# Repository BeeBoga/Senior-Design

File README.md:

# Senior-Design
These are the files utilized in my senior design project which includes a PCB board design provided here, and integration with an arduino Mega 2560.
The main code that I believe is beneficial here would be the code used for the TLC5955 LED driver. There was not much information out there when I begain working on this at the time.
I was able to write functions to bit-bang the colors and intensity I wanted at "fast" speeds for an arduino since I used register manipulation directly

NOTE: the register manipulation will only translate perfectly to the same atmel chip used on said arduino board.

I have not gone back and cleaned this up, but I figured that I take from plenty of broken thoughts in the open-source world so I might as well give back what I have just sitting around incase it's useful to someone

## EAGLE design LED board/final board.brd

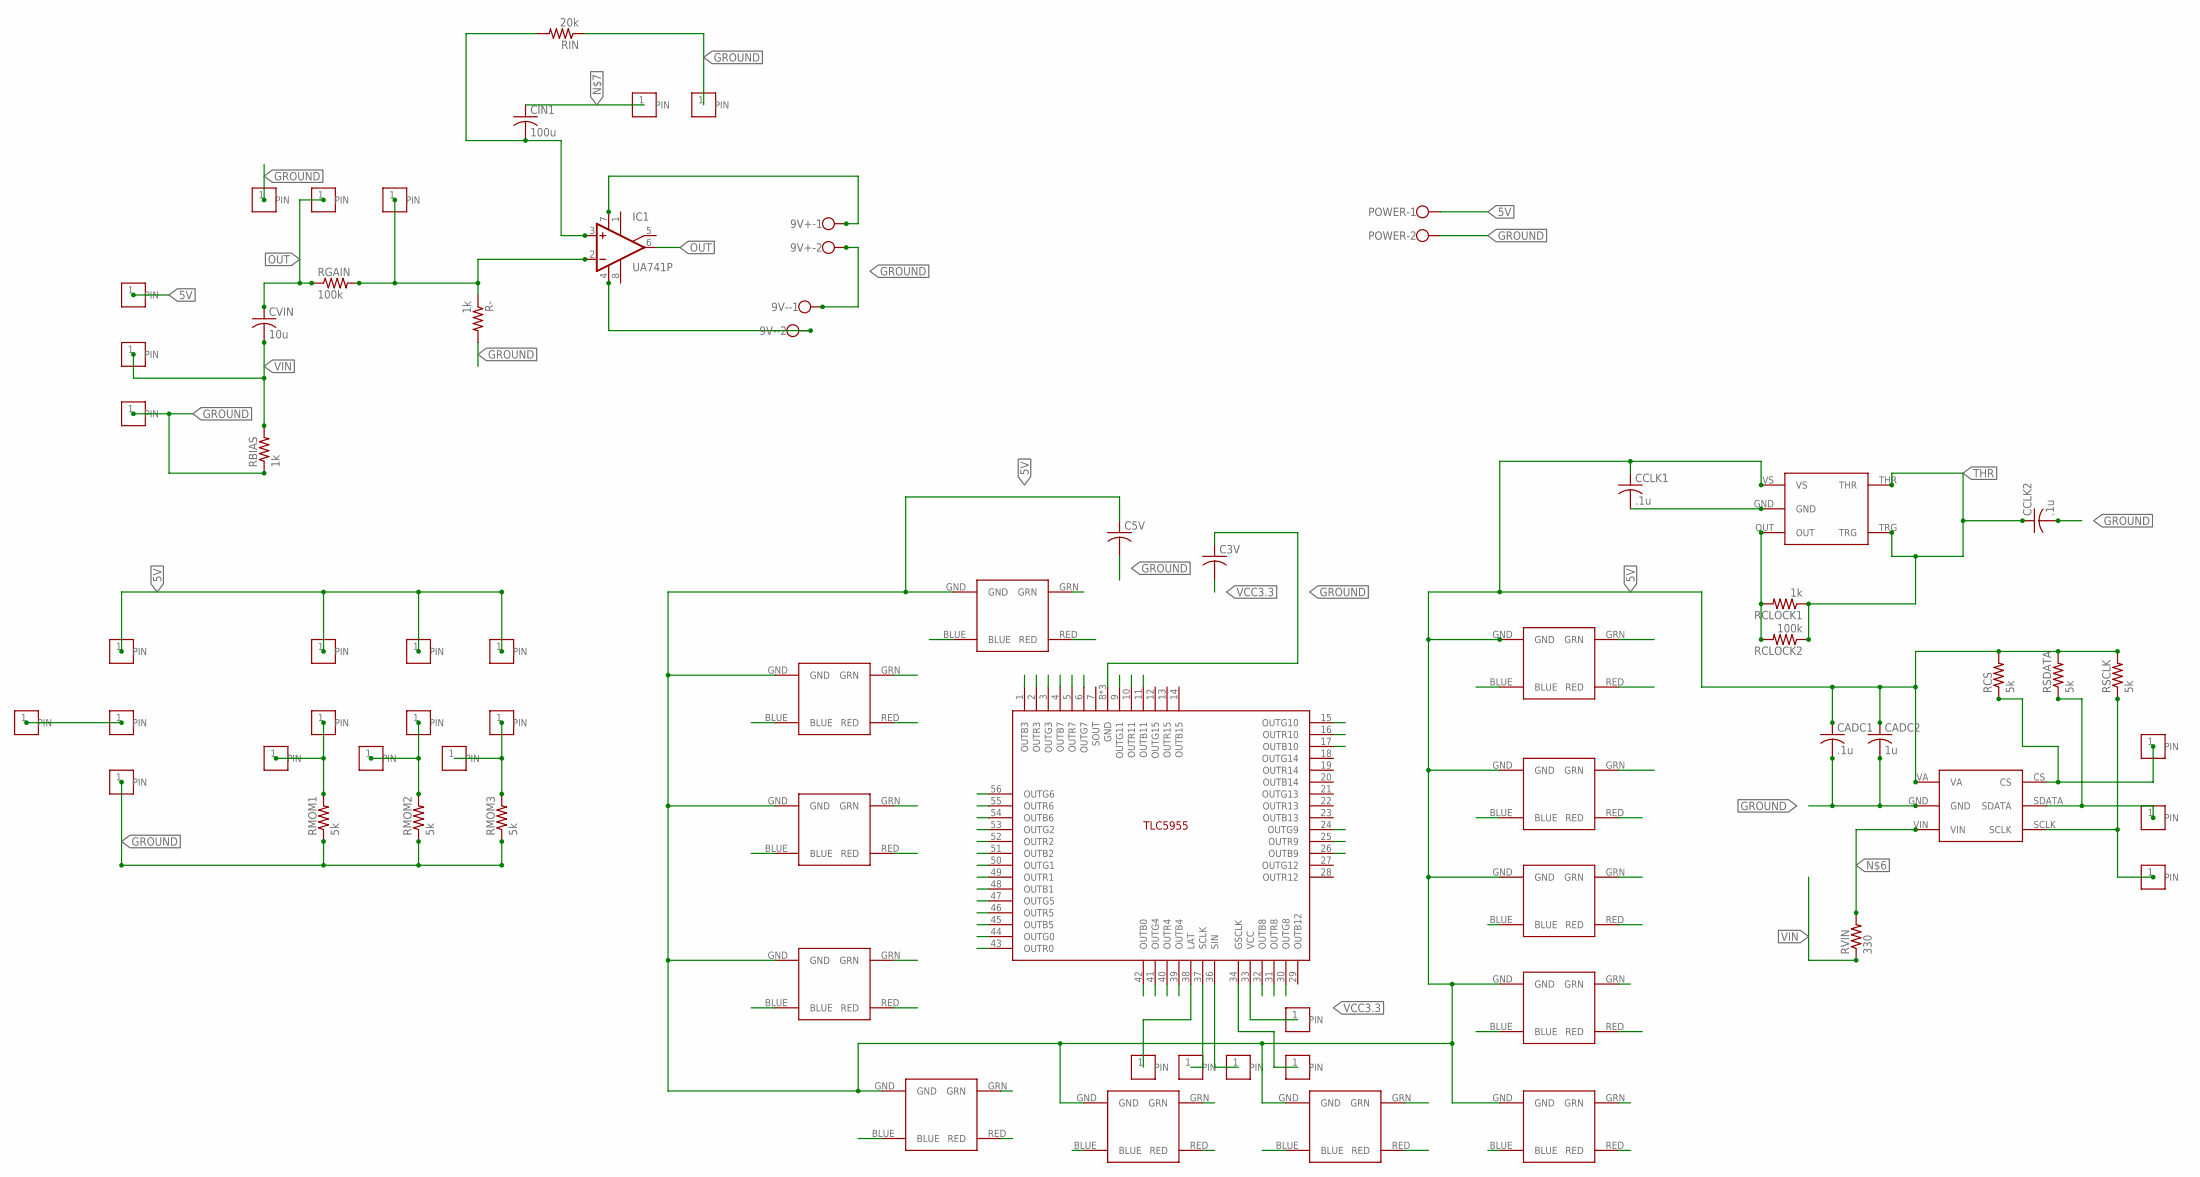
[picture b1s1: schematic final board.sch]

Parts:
3.3V: HEADERPIN_1
9V+, 9V-: W237-102
C3V, C5V: C-USC0805; C0805
CADC1: .1u; C0805
CADC2: 1u; C0805
CCLK1, CCLK2: .1u; C0805
CIN1: 100u; C0805
CS: HEADERPIN_1
CVIN: 10u; C0805
DATA: HEADERPIN_1
GSCLK: HEADERPIN_1
IC1: UA741P; DIL08
INPUTGND: HEADERPIN_1
INPUTV: HEADERPIN_1
INT1, INT2, INT3: HEADERPIN_1
LAT: HEADERPIN_1
MOMA1, MOMA2, MOMA3: HEADERPIN_1
MOMB1, MOMB2, MOMB3: HEADERPIN_1
POTAMPGND: HEADERPIN_1
POTAMPVAL: HEADERPIN_1
POTAMPVCC: HEADERPIN_1
POTBIAS5V: HEADERPIN_1
POTBIASGND: HEADERPIN_1
POTBIASVAL: HEADERPIN_1
POTLVL5V: HEADERPIN_1
POTLVLGND: HEADERPIN_1
POTLVLVAL, POTLVLVAL2: HEADERPIN_1
POWER: W237-102
R-: 1k; M0805
RBIAS: 1k; M0805
RCLOCK1: 1k; M0805
RCLOCK2: 100k; M0805
RCS: 5k; M0805
RGAIN: 100k; M0805
RIN: 20k; M0805
RMOM1, RMOM2, RMOM3: 5k; M0805
RSCLK: 5k; M0805
RSDATA: 5k; M0805
RVIN: 330; M0805
SCLK: HEADERPIN_1
SIN: HEADERPIN_1
SLK: HEADERPIN_1
TLC5955: TLC5954; TLC5955
U$1: MIC1555; SOT-23
U$2, U$3, U$4, U$5, U$6, U$7, U$8, U$9, U$10, U$11, U$12, U$13: KINGSBRIGHT_LED_3.5X2.8
U$14: ADC121S101; SOT-23(6)

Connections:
5V: C5V.1, CADC1.1, CADC2.1, CCLK1.1, MOMA1.1, MOMA2.1, MOMA3.1, POTBIAS5V.1, POTLVL5V.1, POWER.1, RCS.2, RSCLK.2, RSDATA.2, U$1.VS, U$2.GND, U$3.GND, U$4.GND, U$5.GND, U$6.GND, U$7.GND, U$8.GND, U$9.GND, U$10.GND, U$11.GND, U$12.GND, U$13.GND, U$14.VA
B0: TLC5955.42 (OUTB0), U$13.BLUE
B1: TLC5955.48 (OUTB1), U$12.BLUE
B2: TLC5955.51 (OUTB2), U$11.BLUE
B3: TLC5955.1 (OUTB3), U$10.BLUE
B4: TLC5955.39 (OUTB4), U$9.BLUE
B5: TLC5955.45 (OUTB5), U$8.BLUE
B6: TLC5955.54 (OUTB6), U$7.BLUE
B7: TLC5955.4 (OUTB7), U$6.BLUE
B8: TLC5955.32 (OUTB8), U$5.BLUE
B9: TLC5955.26 (OUTB9), U$4.BLUE
B10: TLC5955.17 (OUTB10), U$3.BLUE
B11: TLC5955.11 (OUTB11), U$2.BLUE
G0: TLC5955.44 (OUTG0), U$13.GRN
G1: TLC5955.50 (OUTG1), U$12.GRN
G2: TLC5955.53 (OUTG2), U$11.GRN
G3: TLC5955.3 (OUTG3), U$10.GRN
G4: TLC5955.41 (OUTG4), U$9.GRN
G5: TLC5955.47 (OUTG5), U$8.GRN
G6: TLC5955.56 (OUTG6), U$7.GRN
G7: TLC5955.6 (OUTG7), U$6.GRN
G8: TLC5955.30 (OUTG8), U$5.GRN
G9: TLC5955.24 (OUTG9), U$4.GRN
G10: TLC5955.15 (OUTG10), U$3.GRN
G11: TLC5955.9 (OUTG11), U$2.GRN
GROUND: 9V+.2, 9V-.1, C3V.1, C5V.2, CADC1.2, CADC2.2, CCLK1.2, CCLK2.2, INPUTGND.1, POTAMPGND.1, POTBIASGND.1, POTLVLGND.1, POWER.2, R-.2, RBIAS.1, RIN.1, RMOM1.1, RMOM2.1, RMOM3.1, TLC5955.8 (GND), TLC5955.35 (GND), TLC5955.HEATSINK (GND), U$1.GND, U$14.GND
GSCLK: GSCLK.1, RCLOCK1.2, RCLOCK2.2, TLC5955.34 (GSCLK), U$1.OUT
LAT: LAT.1, TLC5955.38 (LAT)
unnamed: CS.1, RCS.1, U$14.CS
unnamed: INT1.1, MOMB1.1, RMOM1.2
unnamed: RSCLK.1, SLK.1, U$14.SCLK
unnamed: 9V+.1, IC1.7 (V+)
unnamed: 9V-.2, IC1.4 (V-)
unnamed: RVIN.2, U$14.VIN
unnamed: CIN1.1, INPUTV.1
unnamed: CIN1.2, IC1.3 (+IN), RIN.2
unnamed: IC1.2 (-IN), POTAMPVCC.1, R-.1, RGAIN.2
unnamed: INT2.1, MOMB2.1, RMOM2.2
unnamed: INT3.1, MOMB3.1, RMOM3.2
unnamed: POTLVLVAL.1, POTLVLVAL2.1
OUT: CVIN.1, IC1.6 (OUT), POTAMPVAL.1, RGAIN.1
R0: TLC5955.43 (OUTR0), U$13.RED
R1: TLC5955.49 (OUTR1), U$12.RED
R2: TLC5955.52 (OUTR2), U$11.RED
R3: TLC5955.2 (OUTR3), U$10.RED
R4: TLC5955.40 (OUTR4), U$9.RED
R5: TLC5955.46 (OUTR5), U$8.RED
R6: TLC5955.55 (OUTR6), U$7.RED
R7: TLC5955.5 (OUTR7), U$6.RED
R8: TLC5955.31 (OUTR8), U$5.RED
R9: TLC5955.25 (OUTR9), U$4.RED
R10: TLC5955.16 (OUTR10), U$3.RED
R11: TLC5955.10 (OUTR11), U$2.RED
SCLK: SCLK.1, TLC5955.37 (SCLK)
SDATA: DATA.1, RSDATA.1, U$14.SDATA
SIN: SIN.1, TLC5955.36 (SIN)
THR: CCLK2.1, RCLOCK1.1, RCLOCK2.1, U$1.THR, U$1.TRG
VCC3.3: 3.3V.1, C3V.2, TLC5955.33 (VCC)
VIN: CVIN.2, POTBIASVAL.1, RBIAS.2, RVIN.1

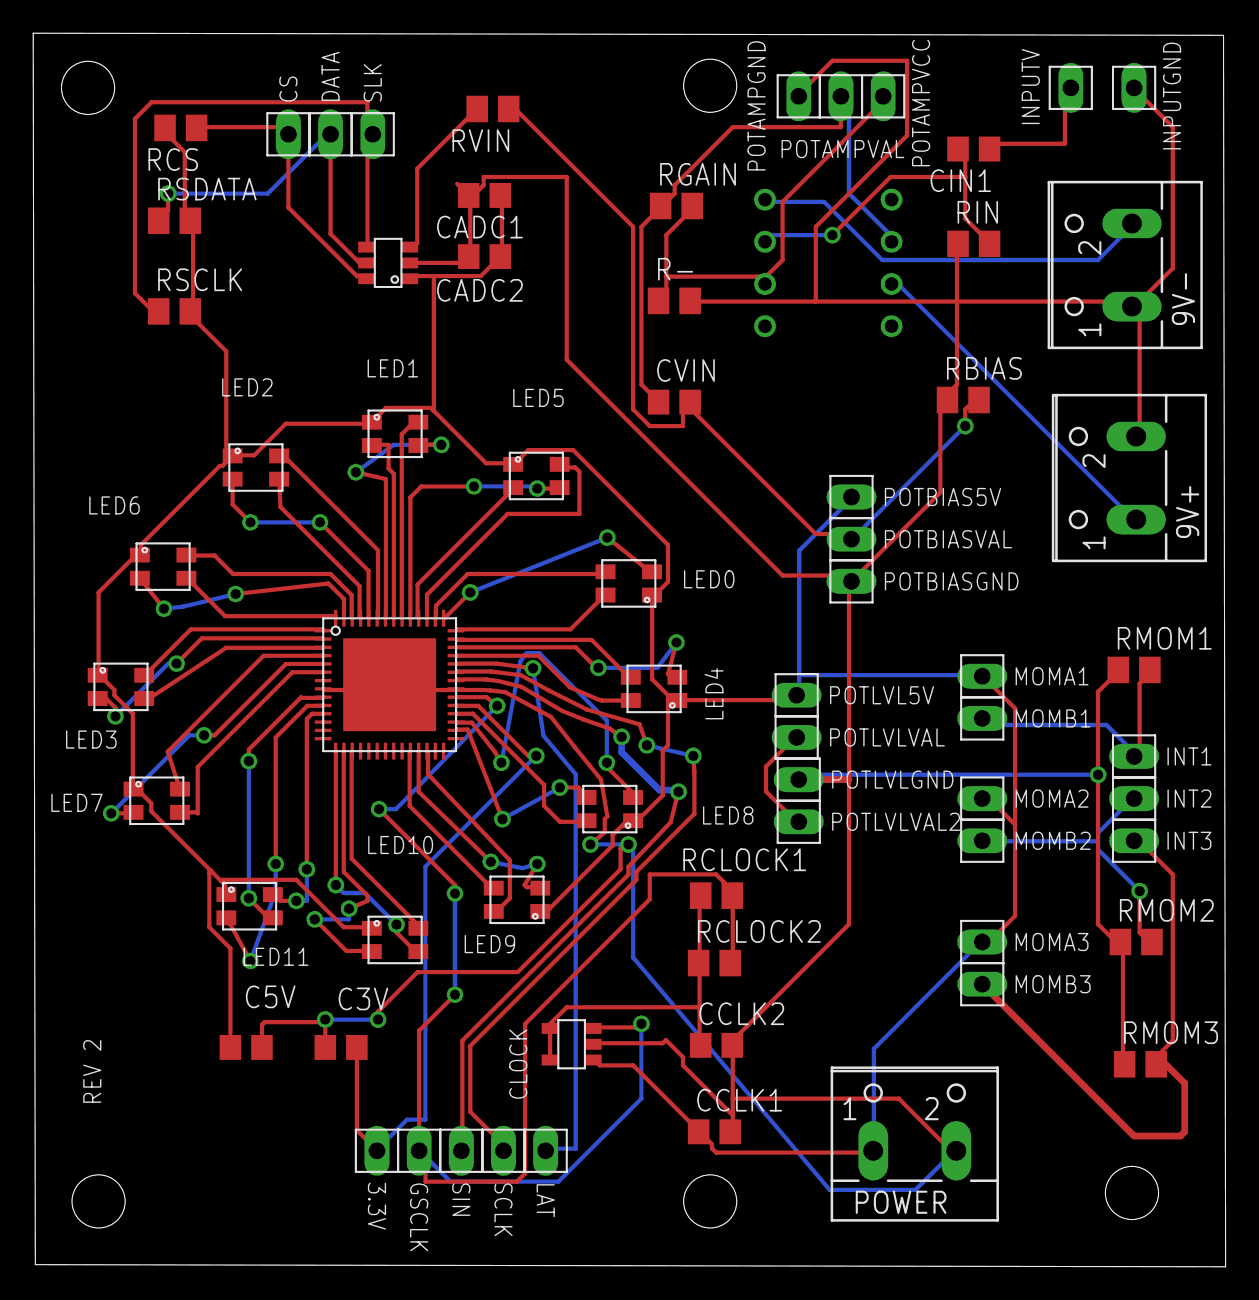
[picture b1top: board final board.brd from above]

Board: 2 copper layers, 71.8 x 74.3 mm, 69 parts (1 on the bottom side), 59 nets.

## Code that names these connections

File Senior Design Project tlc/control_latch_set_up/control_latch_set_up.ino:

#define LAT 7
#define SCLK 6
#define SIN 5
#define GSCLK 4

//769 bit register
//768th bit is control bit 0 sets grayscale
//1 sets dc,mc,bc,fc
//control latch is 371 bits long
//DC data latch is 336 bits long

//bits shift in from 0 towards 769
//in GS each color is 16 bits wide with bit 0 being OUTR0 bit 0 and bit 15 being OUTR0 bit 15

//msb == 1 stores here
//8 bit decoder 767:760
//bits 370:366 FC function control
//bits 365:345 BC global Bright starts at Rn,Gn,then Bn
//bits 344:336 MC max current starts at Rn, Gn, then Bn
//bits 335:0 DC dot correction 7 bits wide each first six are OUTR0



void setup() {
  // put your setup code here, to run once:

  int i, temp;
  int GS [49];
  int settings[769];
  int count =0;
  int times=0;
  int timetemp;
  int FC[5] = {0,0,1,1,1};

  pinMode(2, OUTPUT);

  //analogWrite(2, 128);

  Serial.begin(9600);

  /*
  GS[48]=0;

  for(i=0; i <49;i++)
  {
    if((i%3)==0)
      GS[i]=10000;
    else
      GS[i]=10000;
  }
  */
  
  pinMode(LAT, OUTPUT);
  pinMode(SCLK, OUTPUT);
  pinMode(SIN, OUTPUT);
  pinMode(GSCLK, OUTPUT);
  
  digitalWrite(SCLK, LOW);

  digitalWrite(SIN, HIGH);
  digitalWrite(LAT, LOW);

////////////////////////////////////////////////////////////////////////

sendd(1);

sendd(1);
sendd(0);
sendd(0);
sendd(1);
sendd(0);
sendd(1);
sendd(1);
sendd(0);

for(i=0; i<389; i++)
{
  sendd(1);
}

sendd(0);
sendd(1);
sendd(1);
sendd(1);
sendd(1);



for(i=0; i<7; i++)//bc
{
  sendd(1);
}

sendd(1);//bc
sendd(0);
sendd(0);
sendd(0);
sendd(0);
sendd(0);
sendd(0);

for(i=0; i<7; i++)//bc
{
  sendd(1);
}


for(i=0; i<9; i++)//mc
{
  sendd(1);
}

for(i=0; i<336; i++)//dc
{
  sendd(1);
}

digitalWrite(LAT, HIGH);

digitalWrite(LAT, LOW);

//////////////////////////////////////////////////////////////////////////////////////

sendd(0);

for(i=0; i<720; i++)
{
  sendd(1);
}


for(i=0; i<4; i++)//red
{
  sendd(0);
  sendd(0);
  sendd(1);
  sendd(1);
  
}




for(i=0; i<16; i++)//red
{
  sendd(1);
  
}

/*
//10011010 10011010 b
sendd(0);
sendd(0);
sendd(1);
sendd(1);
sendd(1);
sendd(0);
sendd(1);
sendd(0);

sendd(0);
sendd(0);
sendd(1);
sendd(1);
sendd(1);
sendd(0);
sendd(1);
sendd(0);



//10110111 10110111 g
sendd(1);
sendd(0);
sendd(0);
sendd(1);
sendd(1);
sendd(0);
sendd(1);
sendd(0);

sendd(1);
sendd(0);
sendd(0);
sendd(1);
sendd(1);
sendd(0);
sendd(1);
sendd(0);



//00111010 00111010 r

sendd(1);
sendd(0);
sendd(1);
sendd(1);
sendd(0);
sendd(1);
sendd(1);
sendd(1);

sendd(1);
sendd(0);
sendd(1);
sendd(1);
sendd(0);
sendd(1);
sendd(1);
sendd(1);

*/

//shiftOut(SIN, SCLK, MSBFIRST, 32769);
/*

for(i=0; i<4; i++)//red
{
  sendd(0);
  sendd(0);
  sendd(1);
  sendd(1);
  
}

*/


digitalWrite(LAT, HIGH);

digitalWrite(LAT, LOW);


}

void loop() {
  // put your main code here, to run repeatedly:
  digitalWrite(2,HIGH);
  digitalWrite(2,LOW);

}

void sendd(int in)
{
  digitalWrite(SIN, in);
  digitalWrite(SCLK, 1);
  digitalWrite(SCLK, 0);
}

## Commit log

2017-03-17 :circus_tent: Added .gitattributes
2017-03-17 startup code for the TLC
    first code being added for work
2017-03-21 TLC mostly finished programmed
    TLC 5955 given the easy of programming but with no frequency integration
2017-03-21 This is the actual file
    New easily programmed TLC 5955
2017-03-23 note value return, and frequency capture
2017-03-23 input wave readings
2017-04-06 new and improved
2017-04-13 eagle files
2021-02-24 Create LICENSE
